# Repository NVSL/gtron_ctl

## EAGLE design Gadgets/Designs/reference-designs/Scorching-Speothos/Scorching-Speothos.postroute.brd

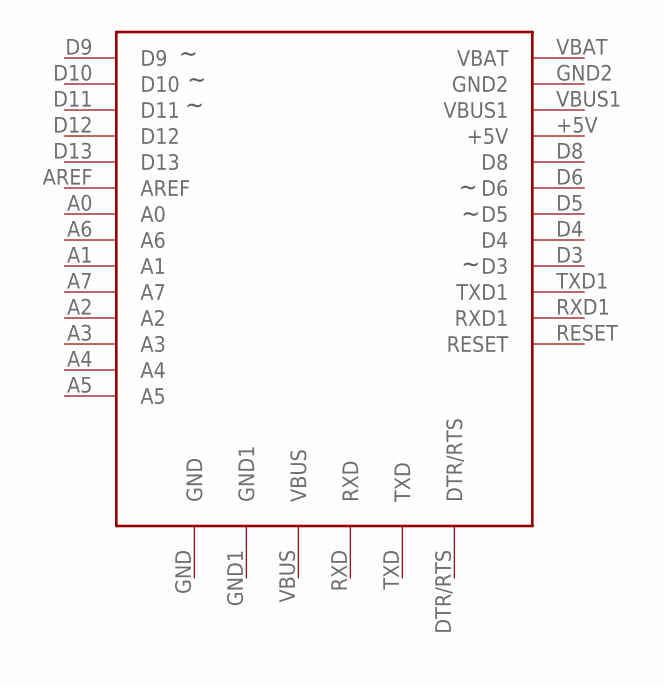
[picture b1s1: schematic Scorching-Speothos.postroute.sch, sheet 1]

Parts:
U4: ADAFRUIT-PRO-TRINKET-5V-BOB; ADAFRUIT-PRO-TRINKET-5V

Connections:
+5V_0_BRAIN: U4.+5V; also elsewhere on the board
A0_0_BRAIN: U4.A0; also elsewhere on the board
A1_0_BRAIN: U4.A1
A2_0_BRAIN: U4.A2
A3_0_BRAIN: U4.A3
A4_0_BRAIN: U4.A4; also elsewhere on the board
A5_0_BRAIN: U4.A5; also elsewhere on the board
A6_0_BRAIN: U4.A6
A7_0_BRAIN: U4.A7
AREF_0_BRAIN: U4.AREF
D3_0_BRAIN: U4.D3; also elsewhere on the board
D4_0_BRAIN: U4.D4; also elsewhere on the board
D5_0_BRAIN: U4.D5; also elsewhere on the board
D6_0_BRAIN: U4.D6; also elsewhere on the board
D8_0_BRAIN: U4.D8; also elsewhere on the board
D9_0_BRAIN: U4.D9; also elsewhere on the board
D10_0_BRAIN: U4.D10; also elsewhere on the board
D11_0_BRAIN: U4.D11; also elsewhere on the board
D12_0_BRAIN: U4.D12; also elsewhere on the board
D13_0_BRAIN: U4.D13; also elsewhere on the board
DTR/RTS_0_BRAIN: U4.DTR/RTS
GND_0_BRAIN: U4.GND, U4.GND1, U4.GND2; also elsewhere on the board
POS_1_BATTERY: U4.VBAT; also elsewhere on the board
RESET_0_BRAIN: U4.RESET
RXD1_0_BRAIN: U4.RXD1
RXD_0_BRAIN: U4.RXD
TXD1_0_BRAIN: U4.TXD1
TXD_0_BRAIN: U4.TXD
VBUS1_0_BRAIN: U4.VBUS1
VBUS_0_BRAIN: U4.VBUS

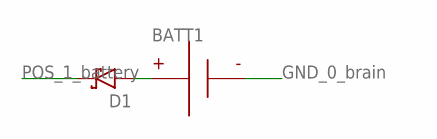
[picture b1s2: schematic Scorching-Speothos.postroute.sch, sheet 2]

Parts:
BATT1: BATTERY-9V-VERTICAL; BATTERY_9V_KEYSTONE_968
D1: RESOLVED-DIODE-SCHOTTKY_TH-DO-41-AND-DO-204AL; DIOAD1125W78L520D270_HS; MPN 1N5817

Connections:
GND_0_BRAIN: BATT1.N; also elsewhere on the board
unnamed: BATT1.P, D1.A
POS_1_BATTERY: D1.C; also elsewhere on the board

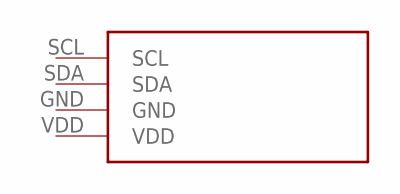
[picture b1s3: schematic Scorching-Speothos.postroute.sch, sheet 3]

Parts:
U7: ADAFRUIT-1.2IN-8X8-LED-BACKPACK-WHITE; ADAFRUIT-1.2IN-8X8-LED-BACKPACK

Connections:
+5V_0_BRAIN: U7.VDD; also elsewhere on the board
A4_0_BRAIN: U7.SDA; also elsewhere on the board
A5_0_BRAIN: U7.SCL; also elsewhere on the board
GND_0_BRAIN: U7.GND; also elsewhere on the board

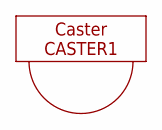
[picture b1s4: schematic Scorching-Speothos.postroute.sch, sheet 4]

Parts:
CASTER1: CASTERADAFRUIT-3/4IN; ADAFRUIT-3/4IN-CASTER

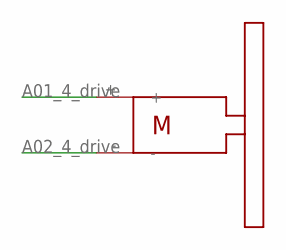
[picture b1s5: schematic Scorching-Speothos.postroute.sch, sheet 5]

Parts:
U1: SOLARBOTICS_GM2SPARKFUN_HOBBY; SPARKFUN_HOBBY_MOTOR

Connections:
A01_4_DRIVE: U1.+; also elsewhere on the board
A02_4_DRIVE: U1.-; also elsewhere on the board

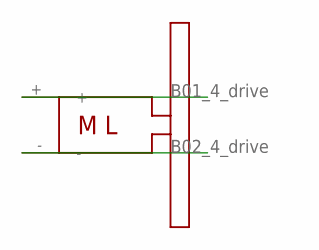
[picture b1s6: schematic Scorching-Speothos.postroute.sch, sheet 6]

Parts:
U2: SOLARBOTICS_GM2_LEFTSPARKFUN_HOBBY; SPARKFUN_HOBBY_MOTOR_LEFT

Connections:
B01_4_DRIVE: U2.+; also elsewhere on the board
B02_4_DRIVE: U2.-; also elsewhere on the board

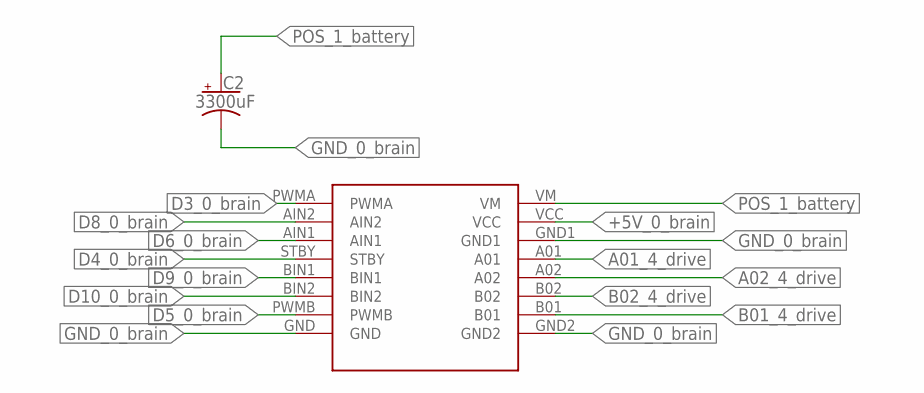
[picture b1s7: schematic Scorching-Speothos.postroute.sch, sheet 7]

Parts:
C2: 3300uF; CAPPRD750W80D1600H2200P; MPN ECA-1EM332
U6: SPARKFUN_DUAL_MOTOR_DRIVER-BOB; SPARKFUN_DUAL_MOTOR_DRIVER

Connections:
+5V_0_BRAIN: U6.VCC; also elsewhere on the board
A01_4_DRIVE: U6.A01; also elsewhere on the board
A02_4_DRIVE: U6.A02; also elsewhere on the board
B01_4_DRIVE: U6.B01; also elsewhere on the board
B02_4_DRIVE: U6.B02; also elsewhere on the board
D3_0_BRAIN: U6.PWMA; also elsewhere on the board
D4_0_BRAIN: U6.STBY; also elsewhere on the board
D5_0_BRAIN: U6.PWMB; also elsewhere on the board
D6_0_BRAIN: U6.AIN1; also elsewhere on the board
D8_0_BRAIN: U6.AIN2; also elsewhere on the board
D9_0_BRAIN: U6.BIN1; also elsewhere on the board
D10_0_BRAIN: U6.BIN2; also elsewhere on the board
GND_0_BRAIN: C2.2 (-), U6.GND, U6.GND1, U6.GND2; also elsewhere on the board
POS_1_BATTERY: C2.1 (+), U6.VM; also elsewhere on the board

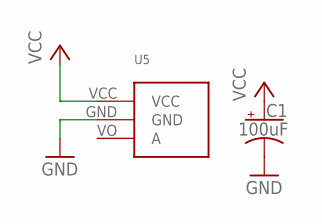
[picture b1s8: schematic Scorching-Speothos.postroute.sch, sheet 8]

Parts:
C1: 100uF; CAPPRD250W80D630H1220P; MPN ECA-1EM101
U5: ANALOG_DISTANCE_SENSOR-GLUE; ANALOG_DISTANCE_SENSOR_GLUE_MOUNT

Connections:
+5V_0_BRAIN: C1.1 (+), U5.VCC; also elsewhere on the board
A0_0_BRAIN: U5.VO (A); also elsewhere on the board
GND_0_BRAIN: C1.2 (-), U5.GND; also elsewhere on the board

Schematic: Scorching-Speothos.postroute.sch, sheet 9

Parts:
LED1: LED-5MM-WHITE; LED5MM
R1: 330; RESAD770W45L370D210_HS; MPN CFR-12JB-52-330R

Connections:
D11_0_BRAIN: LED1.A; also elsewhere on the board
GND_0_BRAIN: R1.2; also elsewhere on the board
unnamed: LED1.K (C), R1.1

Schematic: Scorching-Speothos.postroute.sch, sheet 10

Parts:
U8: BUMP_SWITCH-MEDIUM-LEFT; BUMP_SWITCH_OMRON_D2FLA

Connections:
D12_0_BRAIN: U8.A; also elsewhere on the board
GND_0_BRAIN: U8.B; also elsewhere on the board

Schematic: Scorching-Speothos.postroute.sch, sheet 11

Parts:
U3: BUMP_SWITCH-MEDIUM-RIGHT; BUMP_SWITCH_OMRON_D2FLA1

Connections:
D13_0_BRAIN: U3.A; also elsewhere on the board
GND_0_BRAIN: U3.B; also elsewhere on the board

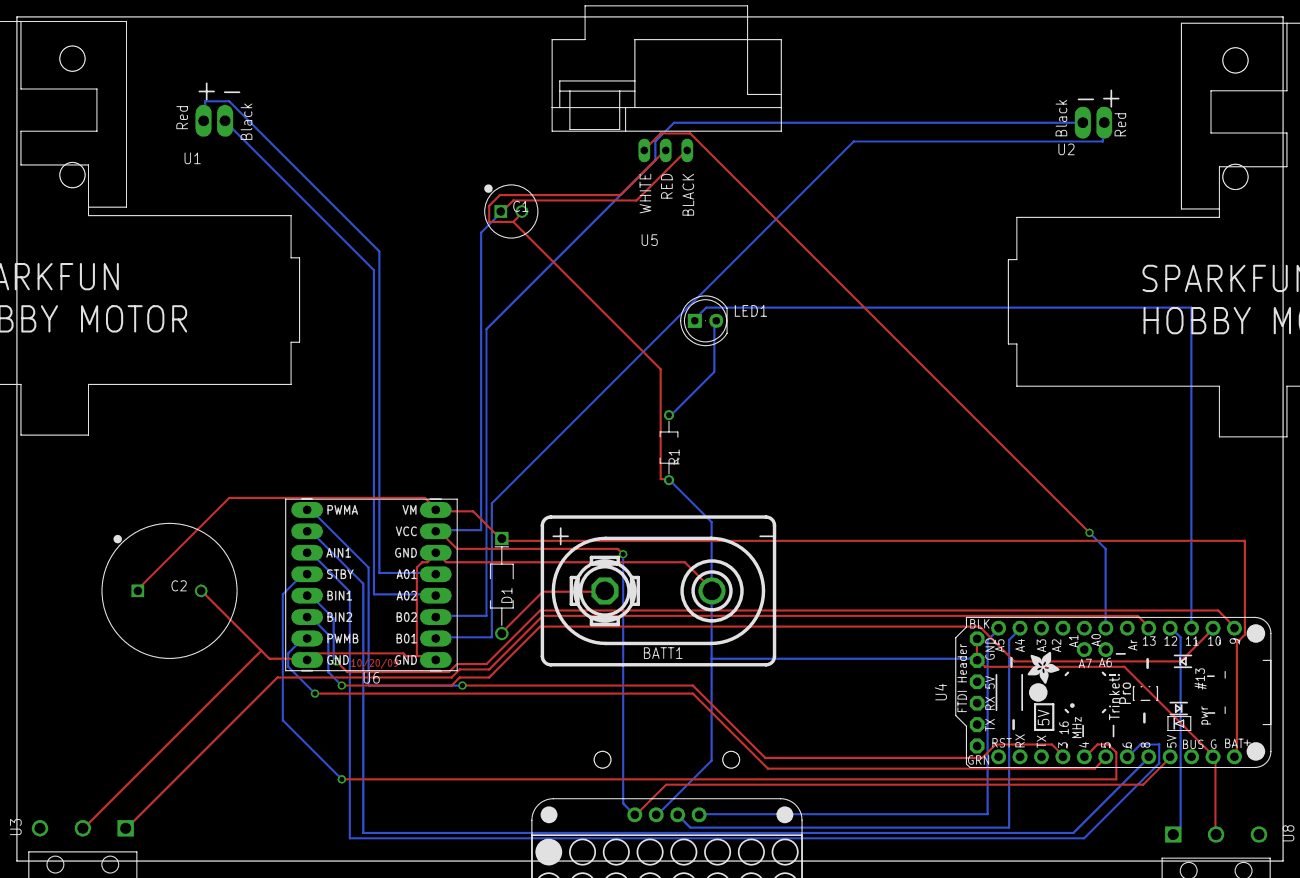
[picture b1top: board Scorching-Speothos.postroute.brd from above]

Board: 2 copper layers, 150.0 x 100.0 mm, 16 parts (1 on the bottom side), 22 nets.

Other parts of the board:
LOGO: BUILT_WITH_GADGETRON

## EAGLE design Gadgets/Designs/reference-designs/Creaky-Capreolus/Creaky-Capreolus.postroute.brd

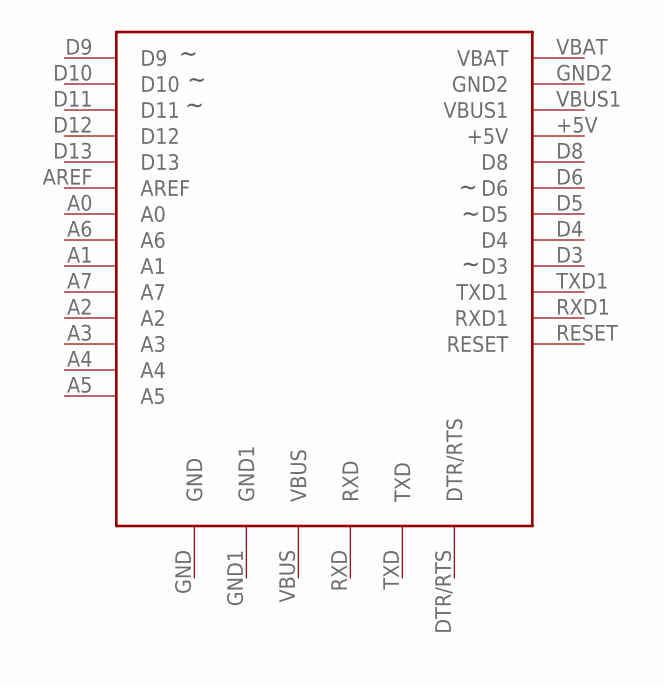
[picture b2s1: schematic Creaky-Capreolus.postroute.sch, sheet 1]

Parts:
U4: ADAFRUIT-PRO-TRINKET-5V-BOB; ADAFRUIT-PRO-TRINKET-5V

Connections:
+5V_0_BRAIN: U4.+5V; also elsewhere on the board
A0_0_BRAIN: U4.A0; also elsewhere on the board
A1_0_BRAIN: U4.A1; also elsewhere on the board
A2_0_BRAIN: U4.A2; also elsewhere on the board
A3_0_BRAIN: U4.A3; also elsewhere on the board
A4_0_BRAIN: U4.A4; also elsewhere on the board
A5_0_BRAIN: U4.A5; also elsewhere on the board
A6_0_BRAIN: U4.A6
A7_0_BRAIN: U4.A7
AREF_0_BRAIN: U4.AREF
D3_0_BRAIN: U4.D3; also elsewhere on the board
D4_0_BRAIN: U4.D4; also elsewhere on the board
D5_0_BRAIN: U4.D5; also elsewhere on the board
D6_0_BRAIN: U4.D6; also elsewhere on the board
D8_0_BRAIN: U4.D8; also elsewhere on the board
D9_0_BRAIN: U4.D9; also elsewhere on the board
D10_0_BRAIN: U4.D10; also elsewhere on the board
D11_0_BRAIN: U4.D11; also elsewhere on the board
D12_0_BRAIN: U4.D12; also elsewhere on the board
D13_0_BRAIN: U4.D13; also elsewhere on the board
DTR/RTS_0_BRAIN: U4.DTR/RTS
GND_0_BRAIN: U4.GND, U4.GND1, U4.GND2; also elsewhere on the board
POS_1_BATTERY: U4.VBAT; also elsewhere on the board
RESET_0_BRAIN: U4.RESET
RXD1_0_BRAIN: U4.RXD1
RXD_0_BRAIN: U4.RXD
TXD1_0_BRAIN: U4.TXD1
TXD_0_BRAIN: U4.TXD
VBUS1_0_BRAIN: U4.VBUS1
VBUS_0_BRAIN: U4.VBUS

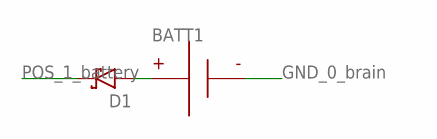
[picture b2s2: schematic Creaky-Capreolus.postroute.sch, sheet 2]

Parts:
BATT1: BATTERY-9V-VERTICAL; BATTERY_9V_KEYSTONE_968
D1: RESOLVED-DIODE-SCHOTTKY_TH-DO-41-AND-DO-204AL; DIOAD1125W78L520D270_HS; MPN 1N5817

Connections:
GND_0_BRAIN: BATT1.N; also elsewhere on the board
unnamed: BATT1.P, D1.A
POS_1_BATTERY: D1.C; also elsewhere on the board

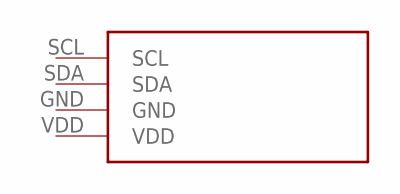
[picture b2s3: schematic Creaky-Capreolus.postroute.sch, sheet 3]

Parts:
U6: ADAFRUIT-7SEG-BACKPACK-RED; ADAFRUIT-7SEG-BACKPACK

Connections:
+5V_0_BRAIN: U6.VDD; also elsewhere on the board
A4_0_BRAIN: U6.SDA; also elsewhere on the board
A5_0_BRAIN: U6.SCL; also elsewhere on the board
GND_0_BRAIN: U6.GND; also elsewhere on the board

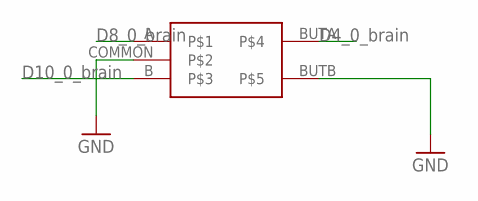
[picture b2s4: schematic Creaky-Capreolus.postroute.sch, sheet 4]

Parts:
U3: ROTARY-ENCODER-W/BUTTON-ADAFRUIT377

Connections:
D4_0_BRAIN: U3.BUTA; also elsewhere on the board
D8_0_BRAIN: U3.A; also elsewhere on the board
D10_0_BRAIN: U3.B; also elsewhere on the board
GND_0_BRAIN: U3.BUTB, U3.COMMON; also elsewhere on the board

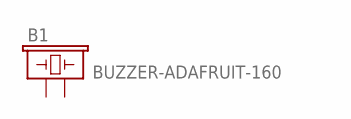
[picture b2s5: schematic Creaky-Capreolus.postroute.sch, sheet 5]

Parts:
B1: BUZZER-ADAFRUIT-160; BUZZER-12MM-ADAFRUIT-160

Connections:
D3_0_BRAIN: B1.+ (1); also elsewhere on the board
GND_0_BRAIN: B1.- (2); also elsewhere on the board

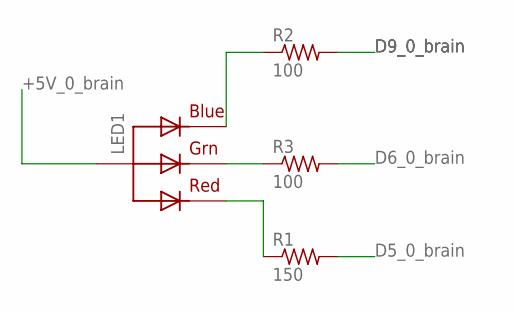
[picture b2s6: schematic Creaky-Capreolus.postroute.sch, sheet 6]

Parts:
LED1: RGBLED_CA-5MM; LED5MMRGB
R1: 150; RESAD770W45L370D210_HS; MPN CFR-12JB-52-150R
R2, R3: 100; RESAD770W45L370D210_HS; MPN CFR-12JB-52-100R

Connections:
+5V_0_BRAIN: LED1.2 (VCC); also elsewhere on the board
D5_0_BRAIN: R1.2; also elsewhere on the board
D6_0_BRAIN: R3.2; also elsewhere on the board
D9_0_BRAIN: R2.2; also elsewhere on the board
unnamed: LED1.4 (BLUE), R2.1
unnamed: LED1.3 (GREEN), R3.1
unnamed: LED1.1 (RED), R1.1

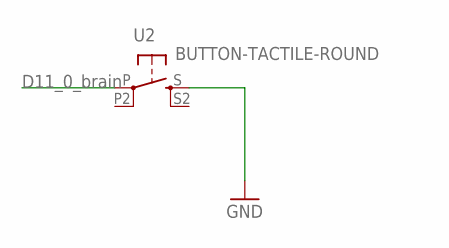
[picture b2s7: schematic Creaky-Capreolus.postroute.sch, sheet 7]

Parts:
U2: BUTTON-TACTILE-ROUND; BUTTON-TACTILE-ROUND-ADAFRUIT1009

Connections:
D11_0_BRAIN: U2.P; also elsewhere on the board
GND_0_BRAIN: U2.S; also elsewhere on the board

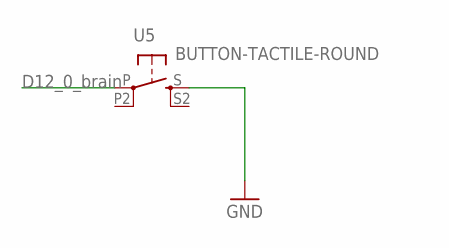
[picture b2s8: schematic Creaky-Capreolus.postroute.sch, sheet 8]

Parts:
U5: BUTTON-TACTILE-ROUND; BUTTON-TACTILE-ROUND-ADAFRUIT1009

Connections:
D12_0_BRAIN: U5.P; also elsewhere on the board
GND_0_BRAIN: U5.S; also elsewhere on the board

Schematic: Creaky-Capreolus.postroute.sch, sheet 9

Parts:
U1: PROTO-AREA-10X10

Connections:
+5V_0_BRAIN: U1.P$11 (VCC), U1.P$12 (VCC), U1.P$13 (VCC), U1.P$14 (VCC), U1.P$15 (VCC), U1.P$16 (VCC), U1.P$17 (VCC), U1.P$18 (VCC), U1.P$19 (VCC), U1.P$20 (VCC); also elsewhere on the board
GND_0_BRAIN: U1.P$1 (GND), U1.P$2 (GND), U1.P$3 (GND), U1.P$4 (GND), U1.P$5 (GND), U1.P$6 (GND), U1.P$7 (GND), U1.P$8 (GND), U1.P$9 (GND), U1.P$10 (GND); also elsewhere on the board

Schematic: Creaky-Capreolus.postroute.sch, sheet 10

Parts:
J2: HEADER-0.1IN-2POS-FEMALE; HDRV2W63P254_2X1_508X254H838_HS

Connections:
A0_0_BRAIN: J2.2; also elsewhere on the board
GND_0_BRAIN: J2.1; also elsewhere on the board

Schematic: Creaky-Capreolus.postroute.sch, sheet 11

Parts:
J3: HEADER-0.1IN-2POS-FEMALE; HDRV2W63P254_2X1_508X254H838_HS

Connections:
D13_0_BRAIN: J3.2; also elsewhere on the board
GND_0_BRAIN: J3.1; also elsewhere on the board

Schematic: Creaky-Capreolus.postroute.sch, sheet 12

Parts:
J4: HEADER-0.1IN-2POS-FEMALE; HDRV2W63P254_2X1_508X254H838_HS

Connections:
+5V_0_BRAIN: J4.2; also elsewhere on the board
GND_0_BRAIN: J4.1; also elsewhere on the board

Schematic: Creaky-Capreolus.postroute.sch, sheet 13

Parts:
J1: HEADER-0.1IN-5POS-FEMALE; HDRV5W63P254_5X1_1270X254H838_HS

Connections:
+5V_0_BRAIN: J1.2; also elsewhere on the board
A1_0_BRAIN: J1.3; also elsewhere on the board
A2_0_BRAIN: J1.4; also elsewhere on the board
A3_0_BRAIN: J1.5; also elsewhere on the board
GND_0_BRAIN: J1.1; also elsewhere on the board

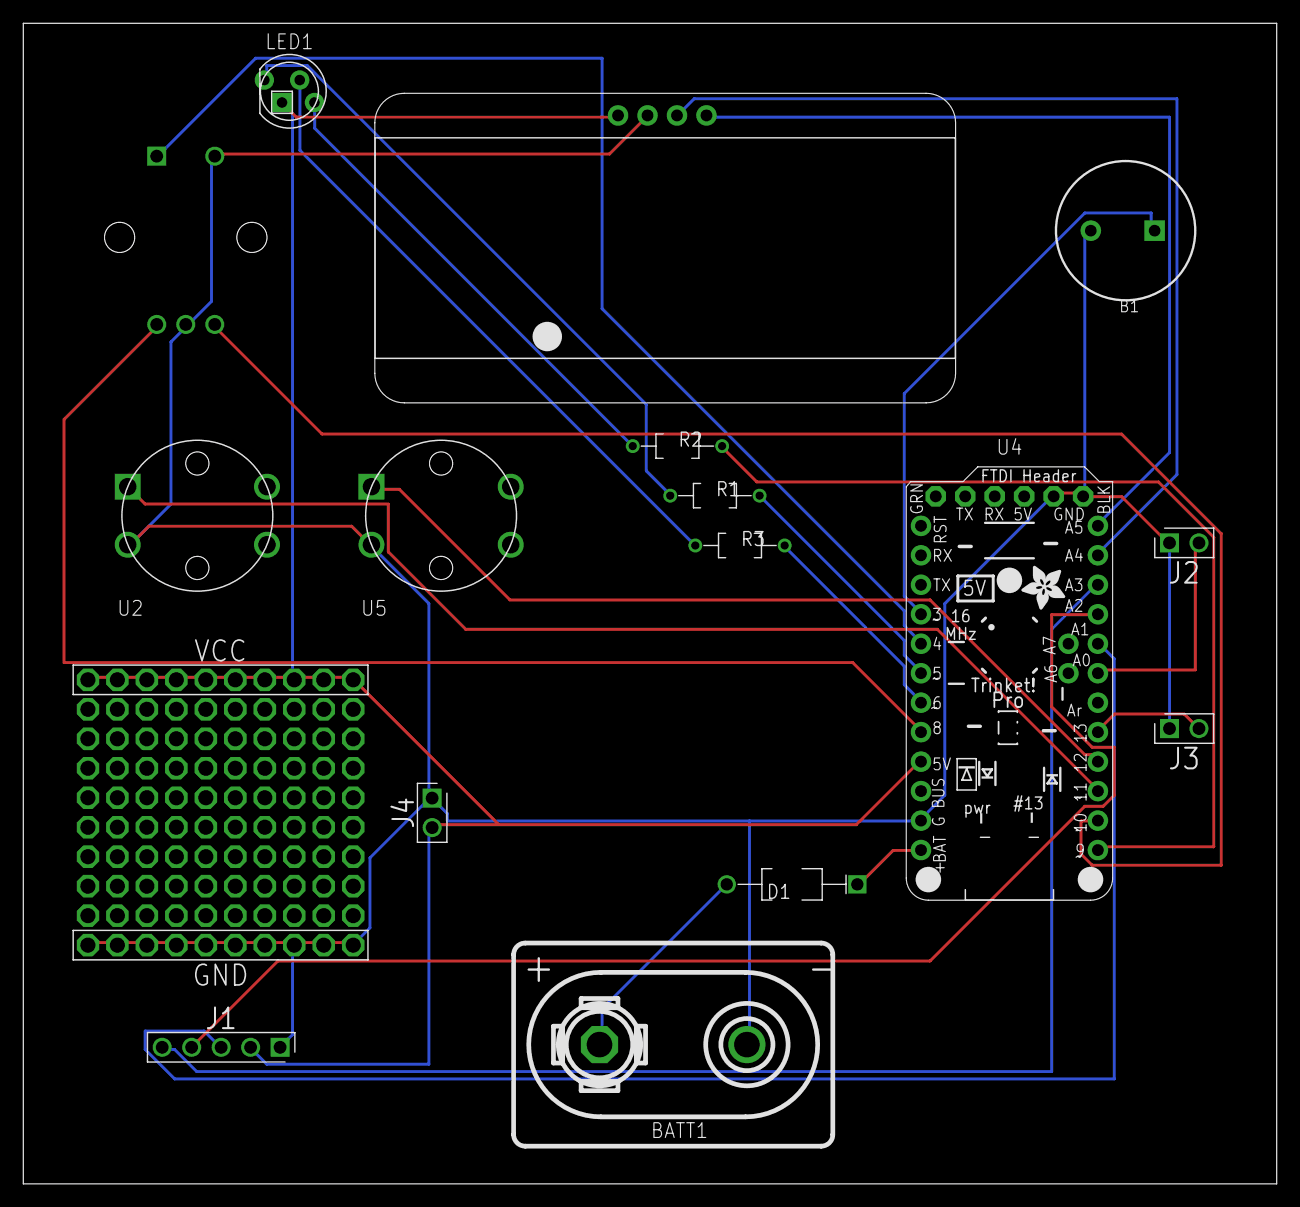
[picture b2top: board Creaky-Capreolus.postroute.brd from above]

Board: 2 copper layers, 108.0 x 100.0 mm, 18 parts (1 on the bottom side), 23 nets.

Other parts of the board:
LOGO: BUILT_WITH_GADGETRON

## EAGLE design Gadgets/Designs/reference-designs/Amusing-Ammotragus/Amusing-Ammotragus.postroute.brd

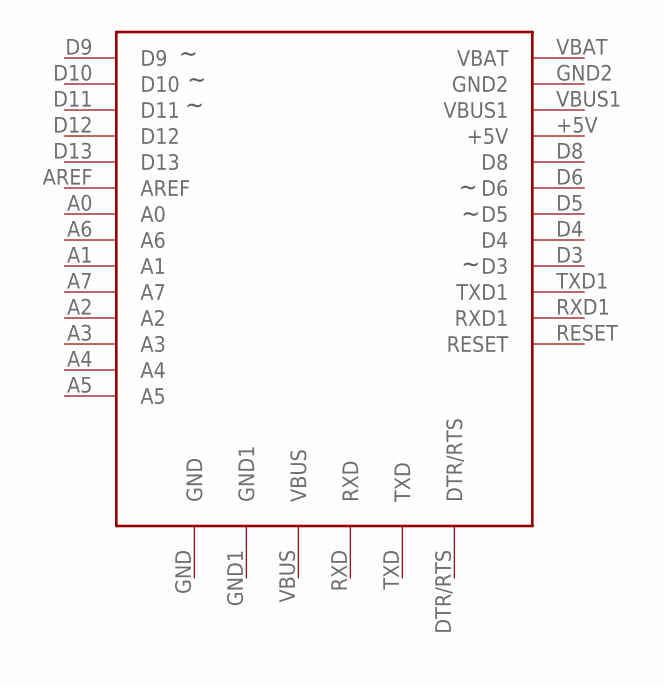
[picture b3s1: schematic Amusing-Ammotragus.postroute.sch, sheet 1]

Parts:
U4: ADAFRUIT-PRO-TRINKET-5V-BOB; ADAFRUIT-PRO-TRINKET-5V

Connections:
+5V_0_BRAIN: U4.+5V; also elsewhere on the board
A0_0_BRAIN: U4.A0; also elsewhere on the board
A1_0_BRAIN: U4.A1
A2_0_BRAIN: U4.A2
A3_0_BRAIN: U4.A3
A4_0_BRAIN: U4.A4; also elsewhere on the board
A5_0_BRAIN: U4.A5; also elsewhere on the board
A6_0_BRAIN: U4.A6
A7_0_BRAIN: U4.A7
AREF_0_BRAIN: U4.AREF
D3_0_BRAIN: U4.D3; also elsewhere on the board
D4_0_BRAIN: U4.D4; also elsewhere on the board
D5_0_BRAIN: U4.D5; also elsewhere on the board
D6_0_BRAIN: U4.D6; also elsewhere on the board
D8_0_BRAIN: U4.D8; also elsewhere on the board
D9_0_BRAIN: U4.D9; also elsewhere on the board
D10_0_BRAIN: U4.D10; also elsewhere on the board
D11_0_BRAIN: U4.D11; also elsewhere on the board
D12_0_BRAIN: U4.D12; also elsewhere on the board
D13_0_BRAIN: U4.D13; also elsewhere on the board
DTR/RTS_0_BRAIN: U4.DTR/RTS
GND_0_BRAIN: U4.GND, U4.GND1, U4.GND2; also elsewhere on the board
POS_1_BATTERY: U4.VBAT; also elsewhere on the board
RESET_0_BRAIN: U4.RESET
RXD1_0_BRAIN: U4.RXD1; also elsewhere on the board
RXD_0_BRAIN: U4.RXD
TXD1_0_BRAIN: U4.TXD1; also elsewhere on the board
TXD_0_BRAIN: U4.TXD
VBUS1_0_BRAIN: U4.VBUS1
VBUS_0_BRAIN: U4.VBUS

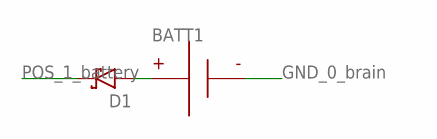
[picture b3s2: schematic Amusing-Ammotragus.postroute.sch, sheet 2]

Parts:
BATT1: BATTERY-9V-VERTICAL; BATTERY_9V_KEYSTONE_968
D1: RESOLVED-DIODE-SCHOTTKY_TH-DO-41-AND-DO-204AL; DIOAD1125W78L520D270_HS; MPN 1N5817

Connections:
GND_0_BRAIN: BATT1.N; also elsewhere on the board
unnamed: BATT1.P, D1.A
POS_1_BATTERY: D1.C; also elsewhere on the board
